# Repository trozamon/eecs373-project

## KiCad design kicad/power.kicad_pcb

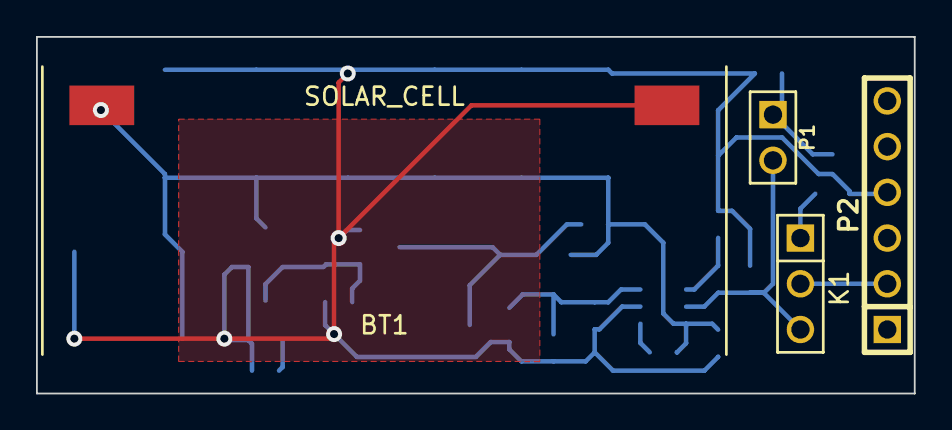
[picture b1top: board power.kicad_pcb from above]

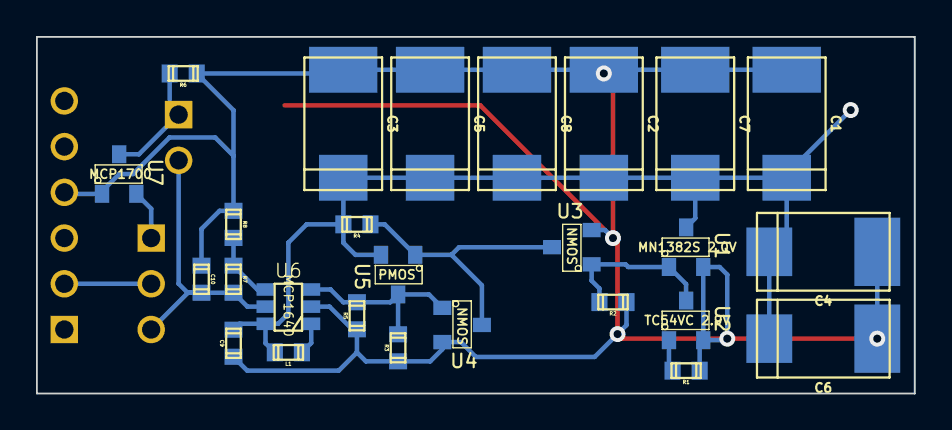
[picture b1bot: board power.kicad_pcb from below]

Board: 2 copper layers, 48.8 x 19.8 mm, 30 parts (26 on the bottom side), 12 nets.

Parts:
BT1: SOLAR_CELL; AM-1417
C1, C2, C3, C4, C5, C6, C7, C8: 100u; c_tant_D
C9: 4.7u; c_0603
C10: 10u; c_0603
K1: VSEL; PIN_ARRAY_3X1
L1: 4.7u; c_0603
P1: 1V8_EN; PIN_ARRAY_2X1
P2: CONN_6; PIN_ARRAY-6X1
R1: 1k; c_0603
R2: 100k; c_0603
R3, R4, R5, R6: 470k; c_0603
R7: 976k; c_0603
R8: 562k; c_0603
U1: MN1382S 2.0V; SOT23
U2: TC54VC 2.9V; SOT23
U3, U4: NMOS; SOT23
U5: PMOS; SOT23
U6: MCP1640; SOT23_6
U7: MCP1700; SOT23

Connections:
GND: BT1.2, C1.2, C2.2, C3.2, C4.2, C5.2, C6.2, C7.2, C8.2, C9.2, C10.2, P2.4, R1.2, R2.2, R3.2, R5.2, R6.2, R8.2, U1.2, U2.2, U3.2, U4.2, U6.2, U7.1
unnamed: C10.1, K1.3, P1.2, R7.1, U6.5
unnamed: K1.2, P2.2
unnamed: K1.1, U7.2
unnamed: R3.1, R5.1, U4.1, U5.3, U6.3
unnamed: L1.2, U6.1
unnamed: R7.2, R8.1, U6.4
unnamed: P1.1, R6.1, U7.3
unnamed: BT1.1, C1.1, C2.1, C3.1, C4.1, C5.1, C6.1, C7.1, C8.1, C9.1, L1.1, R4.1, U1.3, U5.2, U6.6
unnamed: R1.1, U2.1
unnamed: R2.1, U1.1, U2.3, U3.1
unnamed: R4.2, U3.3, U4.3, U5.1

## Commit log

2014-11-02 Add proposal, Makefiles
2014-11-02 Updat Makefile, add pics
2014-11-03 Update diagrams, proposal
2014-11-10 Start system document, it's pretty jank right now.
2014-11-12 Update system document
2014-11-13 Update system documentation
2014-11-16 Add power circuit schematic
2014-11-21 Update power schematic
2014-11-21 Add temp sensor to system docs
2014-11-21 added completed schematic but incomplete board. if you need explanations of parts of the board feel free to ping me
2014-11-21 Finish schematic, assigning footprints
2014-11-21 Finish power component to footprint mapping
2014-11-22 Finalize schematic
2014-11-22 Add initial power board design
2014-11-23 updated files. need to understand new components
2014-11-23 need to route board. 'layout' part done. need eagle professional to finish
2014-11-23 finished layout. let me know if there are glaring errors
2014-11-23 Minor updates to power schematic and board
2014-11-23 Add pull-downs to NMOS gates on power board
2014-11-23 Update gitignore
2014-11-23 finalized soil mite design. sending out for shipping
2014-11-23 Add gerber stuffz
2014-12-03 Redo power schematic
2014-12-03 Finish power schematic bugfixes
2014-12-03 Attach footprints to components
2014-12-03 Small fixes to schematic, netlist
2014-12-03 Layout PCB
2014-12-03 Finish PCB layout
2014-12-03 Update zip generation
2014-12-04 Add nordic chip code.
2014-12-06 add ADC
2014-12-07 Add enclosure v1
2014-12-07 Add initial plotting script, reference power board build files
2014-12-07 Moisture plot is how human-readable
2014-12-07 Start temp sensor, disable prescaling
2014-12-07 Update low bound for time delay in moisture plot
2014-12-08 Add soak data, R script for soak plot
2014-12-08 Update EnclosureBottom
